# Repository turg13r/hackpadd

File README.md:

\# hackpad

This is my hackpad thingy. You can use it by clicking on the keyboard

I made the project cause I really wanted to try using kicad and all this new software.

\# CAD

\# PCB

\# SCHEMATIC

\- 4 Cherry MX Switches

\- 4 DSA Keycaps

\- 4 m3x13mm screws

\- 4 3x5x4 DSA heatset inserts

\- 1 EC11E Rotary Encoder 

\- 1 XIAO SEEED RP2040

\- 2 SK6812 Mini-E LEDs

\- 1 0.91" 128x32 OLED Display

\- 1 Case (2 3d printed parts. top and bottom)

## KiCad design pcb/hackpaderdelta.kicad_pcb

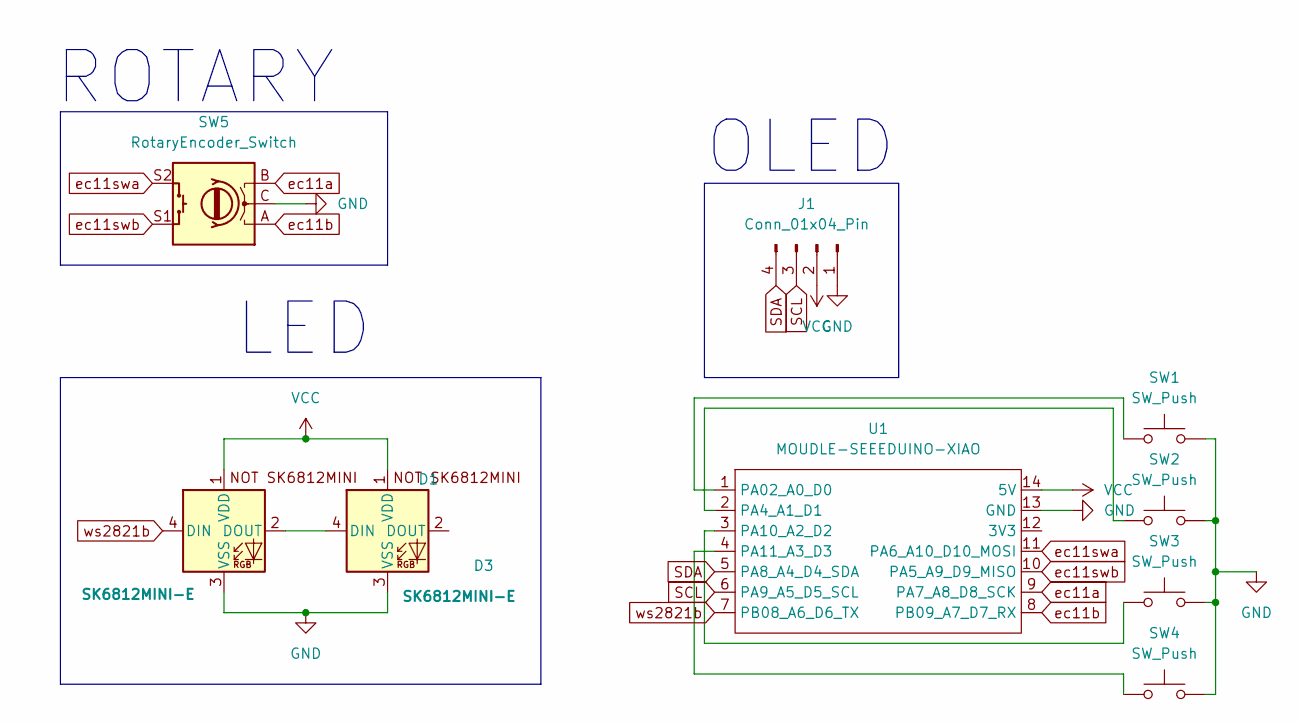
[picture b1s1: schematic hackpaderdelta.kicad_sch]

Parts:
D1, D3: SK6812MINI-E; SK6812MINI-E_fixed
J1: Conn_01x04_Pin; SSD1306-0.91-OLED-4pin-128x32
SW1, SW2, SW3, SW4: SW_Push; SW_Cherry_MX_1.00u_PCB
SW5: RotaryEncoder_Switch; RotaryEncoder_Alps_EC11E-Switch_Vertical_H20mm_CircularMoun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
U1: MOUDLE-SEEEDUINO-XIAO; XIAO-Generic-Hybrid-14P-2.54-21X17.8MM

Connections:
GND: D1.3 (VSS), D3.3 (VSS), J1.1, SW1.2, SW2.2, SW3.2, SW4.2, SW5.C, U1.13 (GND)
unnamed: D1.2 (DOUT), D3.4 (DIN)
unnamed: SW1.1, U1.1 (PA02_A0_D0)
unnamed: SW2.1, U1.2 (PA4_A1_D1)
unnamed: SW3.1, U1.3 (PA10_A2_D2)
unnamed: SW4.1, U1.4 (PA11_A3_D3)
SCL: J1.3, U1.6 (PA9_A5_D5_SCL)
SDA: J1.4, U1.5 (PA8_A4_D4_SDA)
VCC: D1.1 (VDD), D3.1 (VDD), J1.2, U1.14 (5V)
ec11a: SW5.B, U1.9 (PA7_A8_D8_SCK)
ec11b: SW5.A, U1.8 (PB09_A7_D7_RX)
ec11swa: SW5.S2, U1.11 (PA6_A10_D10_MOSI)
ec11swb: SW5.S1, U1.10 (PA5_A9_D9_MISO)
ws2821b: D1.4 (DIN), U1.7 (PB08_A6_D6_TX)

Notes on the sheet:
ROTARY
OLED
LED

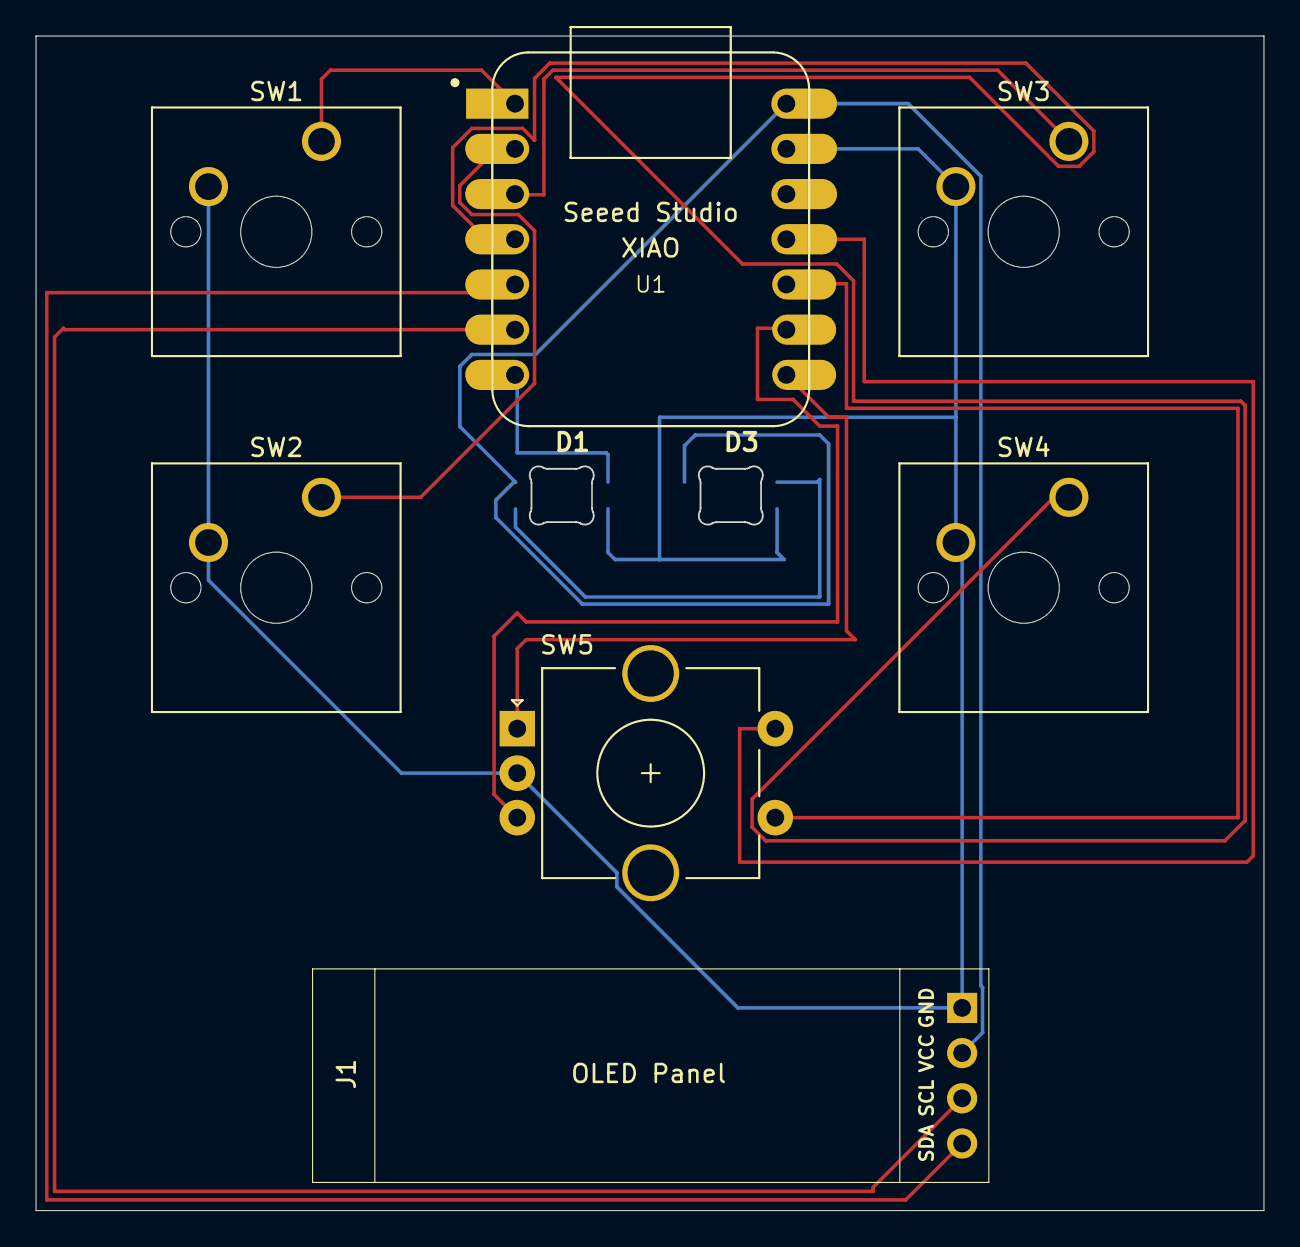
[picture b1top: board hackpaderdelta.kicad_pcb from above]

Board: 2 copper layers, 69.0 x 66.0 mm, 9 parts (0 on the bottom side), 14 nets.

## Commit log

2026-03-17 Yes! A whole 2 day's worth of work..
2026-03-18 yippeee
2026-03-18 good
2026-03-19 Im finally done, at least I hope so. Please :((((
2026-03-20 yes its done its done its done im done
2026-03-22 yipee! 2
2026-03-28 Uhhhh uhhhuhhuh uh huh
